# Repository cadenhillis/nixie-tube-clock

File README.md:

# nixie-tube-clock

custom high-voltage boost power supply and nessesary drivers to control IN-12A and IN13 nixies with an adafruit itsybitsy nRF32

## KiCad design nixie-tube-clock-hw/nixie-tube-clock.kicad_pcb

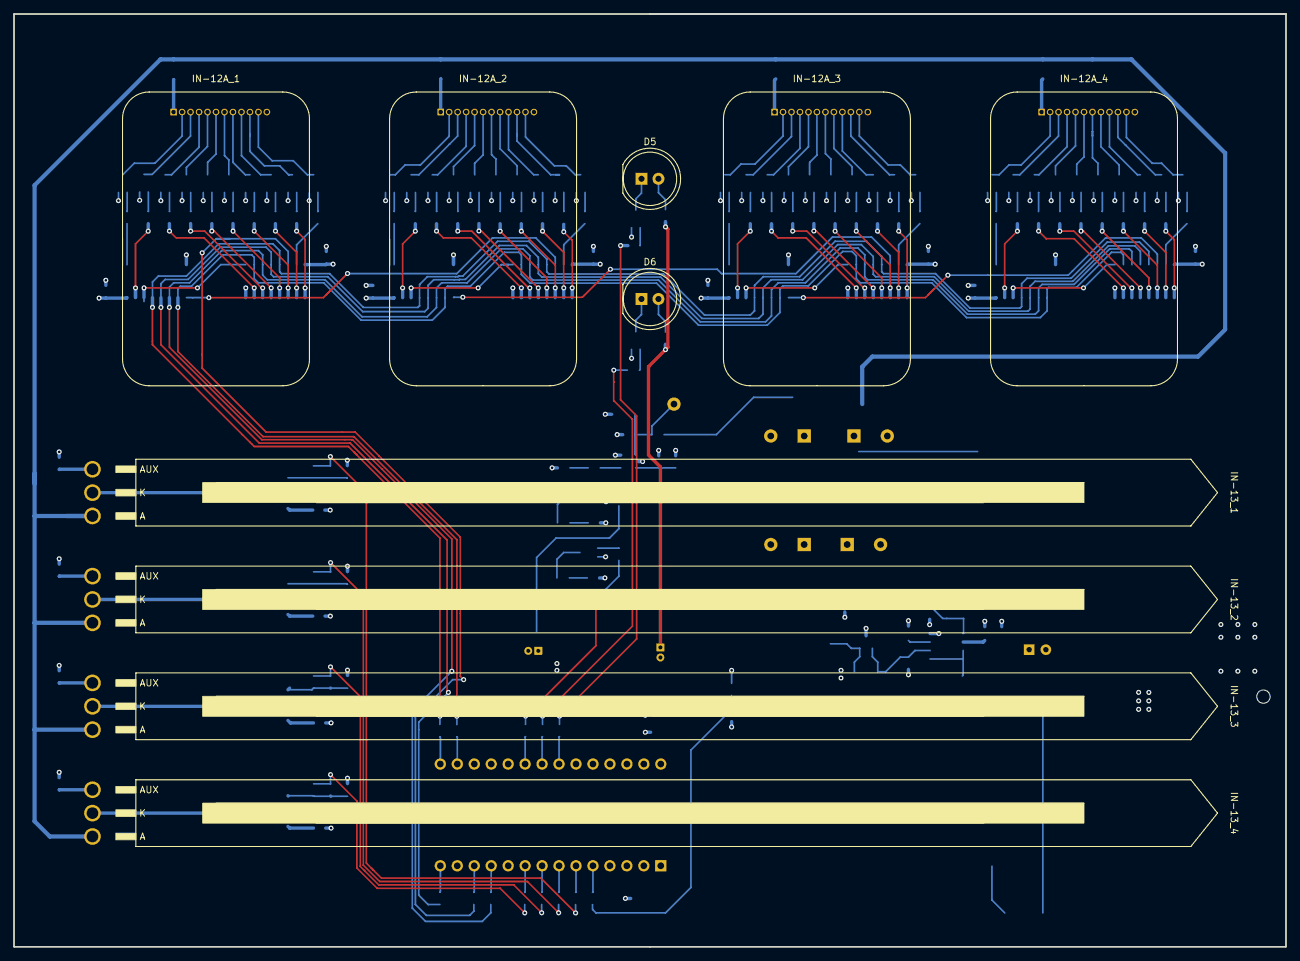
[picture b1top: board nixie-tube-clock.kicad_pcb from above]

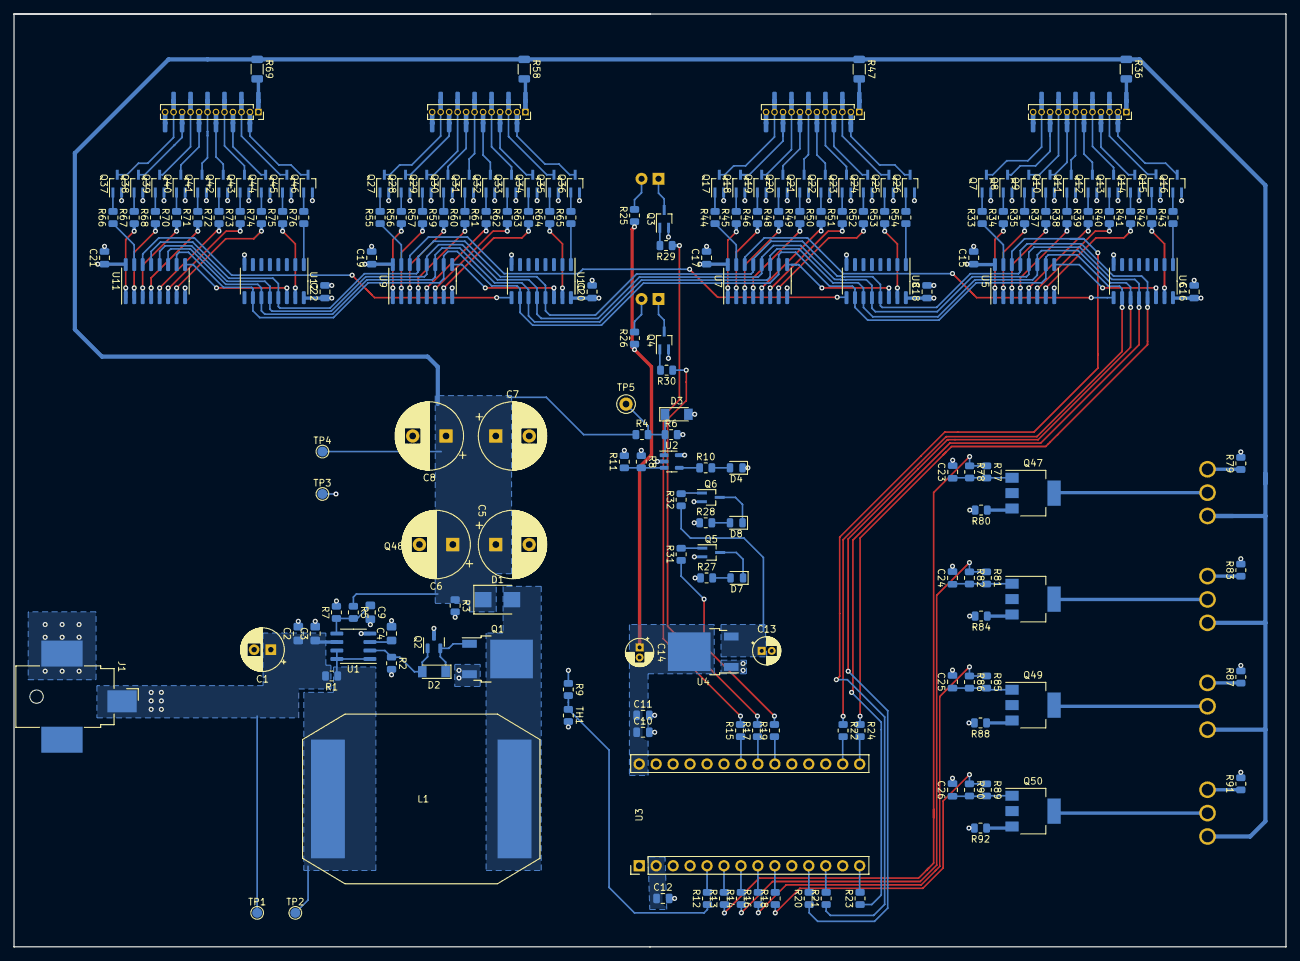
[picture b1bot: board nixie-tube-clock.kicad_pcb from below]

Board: 4 copper layers, 190.5 x 139.7 mm, 204 parts (194 on the bottom side), 200 nets.

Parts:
C1: 47uF; CP_Radial_D6.3mm_P2.50mm
C2: 2.2uF; C_0805_2012Metric_Pad1.18x1.45mm_HandSolder
C3: 0.1uF; C_0805_2012Metric_Pad1.18x1.45mm_HandSolder
C4: 470pF; C_0805_2012Metric_Pad1.18x1.45mm_HandSolder
C5, C6, C7, C8: 4.7uF; CP_Radial_D10.0mm_P5.00mm
C9: 10nF; C_0805_2012Metric_Pad1.18x1.45mm_HandSolder
C10: 1uF; C_0805_2012Metric
C11, C12, C23, C24, C25, C26: 10uF; C_0805_2012Metric
C13, C14: 10uF; CP_Radial_D4.0mm_P1.50mm
C15, C16, C17, C18, C19, C20, C21, C22: 0.1uF; C_0805_2012Metric
D1: SK3200B-LTP; D_SMB
D2: FDLL4148-D87Z; D_MiniMELF
D3: BZV55-C3V3,115; D_MiniMELF
D4, D8: ORANGE; D_0805_2012Metric
D5, D6: ORANGE; LED_D8.0mm
D7: RED; D_0805_2012Metric
IN-12A_1, IN-12A_2, IN-12A_3, IN-12A_4: IN-12A DAUGHTER; nixie_daughter
IN-13_1, IN-13_2, IN-13_3, IN-13_4: IN13; IN-13
J1: PJ-036AH-SMT-TR; BarrelJack_CUI_PJ-036AH-SMT_Horizontal
L1: 1mH; PM2120
Q1: FQD16N25CTM; TO-252-2
Q2: PMBT3906,235; SOT-23
Q3, Q4, Q5, Q6, Q7, Q8, Q9, Q10, Q11, Q12, Q13, Q14, Q15, Q16, Q17, Q18, Q19, Q20, Q21, Q22, Q23, Q24, Q25, Q26, Q27, Q28, Q29, Q30, Q31, Q32, Q33, Q34, Q35, Q36, Q37, Q38, Q39, Q40, Q41, Q42, Q43, Q44, Q45, Q46: MMSTA42-7-F; SOT-323_SC-70_Handsoldering
Q47, Q48, Q49, Q50: FZT857TA; SOT-223-3_TabPin2
R1: 300mR; R_0805_2012Metric
R2: 240; R_0805_2012Metric
R3: 1M; R_0805_2012Metric
R4: 3Meg; R_0805_2012Metric
R5: 200k; R_0805_2012Metric
R6: 20k; R_0805_2012Metric
R7: 1.68k; R_0805_2012Metric
R8: 25k; R_0805_2012Metric
R9, R11: 10k; R_0805_2012Metric
R10, R27, R28: 1.2k; R_0805_2012Metric
R12, R13, R14, R15, R16, R17, R18, R19, R20, R21, R22, R23, R24: 0; R_0805_2012Metric
R25, R26: 220; R_0805_2012Metric
R29, R30, R31: 1.2K; R_0805_2012Metric
R32: 10K; R_0805_2012Metric
R33, R34, R35, R37, R38, R39, R40, R41, R42, R43, R44, R45, R46, R48, R49, R50, R51, R52, R53, R54, R55, R56, R57, R59, R60, R61, R62, R63, R64, R65, R66, R67, R68, R70, R71, R72, R73, R74, R75, R76: 22k; R_0805_2012Metric
R36, R47, R58, R69: R_US; R_1206_3216Metric
R77, R81, R85, R89: 330; R_0805_2012Metric
R78, R82, R86, R90: 4.7k; R_0805_2012Metric
R79, R83, R87, R91: 330k; R_0805_2012Metric
R80, R84, R88, R92: 560; R_0805_2012Metric
TH1: 10k; R_0805_2012Metric
TP1, TP2, TP3, TP4: TestPoint; TestPoint_Pad_D1.5mm
TP5: TestPoint; TestPoint_Keystone_5000-5004_Miniature
U1: MC34063AD; SOIC-8_3.9x4.9mm_P1.27mm
U2: AS321KTR-G1; SOT-23-5
U3: ItsyBitsy_M0_Express; ItsyBitsy
U4: NCP1117IDT50T4G; TO-252-2
U5, U6, U7, U8, U9, U10, U11, U12: 74HC594D,118; SOIC-16_3.9x9.9mm_P1.27mm

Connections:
+3V3: C12.1, C15.1, C16.1, C17.1, C18.1, C19.1, C20.1, C21.1, C22.1, R8.1, R9.1, R27.1, R28.1, U2.5 (V+), U3.2 (3V3), U5.16 (VCC), U6.16 (VCC), U7.16 (VCC), U8.16 (VCC), U9.16 (VCC), U10.16 (VCC), U11.16 (VCC), U12.16 (VCC)
+5V: C10.1, C11.1, C14.1, R25.1, R26.1, U3.28 (BAT), U4.2 (VO)
+12V: C1.1, C2.1, C3.1, C13.1, J1.1, R1.2, R32.1, TP1.1, U1.6 (Vin), U4.3 (VI)
/150V_VA/1v_LED: D3.1 (K), R4.2, R6.1, TP5.1, U2.1 (+)
/COLON_1: R15.2, R29.1
/COLON_2: R17.2, R30.1
/D1/B0: R43.1, U6.1 (Q1)
/D1/B1: R33.1, U5.15 (Q0)
/D1/B2: R34.1, U5.1 (Q1)
/D1/B3: R35.1, U5.2 (Q2)
/D1/B4: R37.1, U5.3 (Q3)
/D1/B5: R38.1, U5.4 (Q4)
/D1/B6: R39.1, U5.5 (Q5)
/D1/B7: R40.1, U5.6 (Q6)
/D1/B8: R41.1, U5.7 (Q7)
/D1/B9: R42.1, U6.15 (Q0)
/D1/DOUT: U6.9 (Q7S), U7.14 (DS)
/D1/K0: IN-12A_1.2 (K_0), Q16.3 (C)
/D1/K1: IN-12A_1.11 (K_1), Q7.3 (C)
/D1/K2: IN-12A_1.10 (K_2), Q8.3 (C)
/D1/K3: IN-12A_1.9 (K_3), Q9.3 (C)
/D1/K4: IN-12A_1.8 (K_4), Q10.3 (C)
/D1/K5: IN-12A_1.7 (K_5), Q11.3 (C)
/D1/K6: IN-12A_1.6 (K_6), Q12.3 (C)
/D1/K7: IN-12A_1.5 (K_7), Q13.3 (C)
/D1/K8: IN-12A_1.4 (K_8), Q14.3 (C)
/D1/K9: IN-12A_1.3 (K_9), Q15.3 (C)
/D2/B0: R54.1, U8.1 (Q1)
/D2/B1: R44.1, U7.15 (Q0)
/D2/B2: R45.1, U7.1 (Q1)
/D2/B3: R46.1, U7.2 (Q2)
/D2/B4: R48.1, U7.3 (Q3)
/D2/B5: R49.1, U7.4 (Q4)
/D2/B6: R50.1, U7.5 (Q5)
/D2/B7: R51.1, U7.6 (Q6)
/D2/B8: R52.1, U7.7 (Q7)
/D2/B9: R53.1, U8.15 (Q0)
/D2/DOUT: U8.9 (Q7S), U9.14 (DS)
/D2/K0: IN-12A_2.2 (K_0), Q26.3 (C)
/D2/K1: IN-12A_2.11 (K_1), Q17.3 (C)
/D2/K2: IN-12A_2.10 (K_2), Q18.3 (C)
/D2/K3: IN-12A_2.9 (K_3), Q19.3 (C)
/D2/K4: IN-12A_2.8 (K_4), Q20.3 (C)
/D2/K5: IN-12A_2.7 (K_5), Q21.3 (C)
/D2/K6: IN-12A_2.6 (K_6), Q22.3 (C)
/D2/K7: IN-12A_2.5 (K_7), Q23.3 (C)
/D2/K8: IN-12A_2.4 (K_8), Q24.3 (C)
/D2/K9: IN-12A_2.3 (K_9), Q25.3 (C)
/D3/B0: R65.1, U10.1 (Q1)
/D3/B1: R55.1, U9.15 (Q0)
/D3/B2: R56.1, U9.1 (Q1)
/D3/B3: R57.1, U9.2 (Q2)
/D3/B4: R59.1, U9.3 (Q3)
/D3/B5: R60.1, U9.4 (Q4)
/D3/B6: R61.1, U9.5 (Q5)
/D3/B7: R62.1, U9.6 (Q6)
/D3/B8: R63.1, U9.7 (Q7)
/D3/B9: R64.1, U10.15 (Q0)
/D3/DOUT: U10.9 (Q7S), U11.14 (DS)
/D3/K0: IN-12A_3.2 (K_0), Q36.3 (C)
/D3/K1: IN-12A_3.11 (K_1), Q27.3 (C)
/D3/K2: IN-12A_3.10 (K_2), Q28.3 (C)
/D3/K3: IN-12A_3.9 (K_3), Q29.3 (C)
/D3/K4: IN-12A_3.8 (K_4), Q30.3 (C)
/D3/K5: IN-12A_3.7 (K_5), Q31.3 (C)
/D3/K6: IN-12A_3.6 (K_6), Q32.3 (C)
/D3/K7: IN-12A_3.5 (K_7), Q33.3 (C)
/D3/K8: IN-12A_3.4 (K_8), Q34.3 (C)
/D3/K9: IN-12A_3.3 (K_9), Q35.3 (C)
/D4/B0: R76.1, U12.1 (Q1)
/D4/B1: R66.1, U11.15 (Q0)
/D4/B2: R67.1, U11.1 (Q1)
/D4/B3: R68.1, U11.2 (Q2)
/D4/B4: R70.1, U11.3 (Q3)
/D4/B5: R71.1, U11.4 (Q4)
/D4/B6: R72.1, U11.5 (Q5)
/D4/B7: R73.1, U11.6 (Q6)
/D4/B8: R74.1, U11.7 (Q7)
/D4/B9: R75.1, U12.15 (Q0)
/D4/K0: IN-12A_4.2 (K_0), Q46.3 (C)
/D4/K1: IN-12A_4.11 (K_1), Q37.3 (C)
/D4/K2: IN-12A_4.10 (K_2), Q38.3 (C)
/D4/K3: IN-12A_4.9 (K_3), Q39.3 (C)
/D4/K4: IN-12A_4.8 (K_4), Q40.3 (C)
/D4/K5: IN-12A_4.7 (K_5), Q41.3 (C)
/D4/K6: IN-12A_4.6 (K_6), Q42.3 (C)
/D4/K7: IN-12A_4.5 (K_7), Q43.3 (C)
/D4/K8: IN-12A_4.4 (K_8), Q44.3 (C)
/D4/K9: IN-12A_4.3 (K_9), Q45.3 (C)
/DAY_PWM: R13.1, R77.1, R78.1
/MONTH_PWM: R16.1, R85.1, R86.1
/MOSI: R21.1, U5.14 (DS)
/SCK: R20.1, U5.11 (SHCP), U6.11 (SHCP), U7.11 (SHCP), U8.11 (SHCP), U9.11 (SHCP), U10.11 (SHCP), U11.11 (SHCP), U12.11 (SHCP)
/STORE: R23.1, U5.12 (STCP), U6.12 (STCP), U7.12 (STCP), U8.12 (STCP), U9.12 (STCP), U10.12 (STCP), U11.12 (STCP), U12.12 (STCP)
/TEMP: R9.2, R12.1, TH1.1
/TEMP_LED: R19.2, R31.1
/WEEK_PWM: R14.1, R81.1, R82.1
/YEAR_PWM: R18.1, R89.1, R90.1
/~CLR_SHIFT: R22.1, U5.10 (~SHR), U6.10 (~SHR), U7.10 (~SHR), U8.10 (~SHR), U9.10 (~SHR), U10.10 (~SHR), U11.10 (~SHR), U12.10 (~SHR)
/~CLR_STORE: R24.1, U5.13 (~STR), U6.13 (~STR), U7.13 (~STR), U8.13 (~STR), U9.13 (~STR), U10.13 (~STR), U11.13 (~STR), U12.13 (~STR)
GND: C1.2, C2.2, C3.2, C4.2, C5.2, C6.2, C7.2, C8.2, C9.2, C10.2, C11.2, C12.2, C13.2, C14.2, C15.2, C16.2, C17.2, C18.2, C19.2, C20.2, C21.2, C22.2, C23.2, C24.2, C25.2, C26.2, D3.2 (A), D4.1 (K), J1.2, Q1.3 (S), Q2.3 (C), Q3.2 (E), Q4.2 (E), Q5.2 (E), Q6.2 (E), Q7.2 (E), Q8.2 (E), Q9.2 (E), Q10.2 (E), Q11.2 (E), Q12.2 (E), Q13.2 (E), Q14.2 (E), Q15.2 (E), Q16.2 (E), Q17.2 (E), Q18.2 (E), Q19.2 (E), Q20.2 (E), Q21.2 (E), Q22.2 (E), Q23.2 (E), Q24.2 (E), Q25.2 (E), Q26.2 (E), Q27.2 (E), Q28.2 (E), Q29.2 (E), Q30.2 (E), Q31.2 (E), Q32.2 (E), Q33.2 (E), Q34.2 (E), Q35.2 (E), Q36.2 (E), Q37.2 (E), Q38.2 (E), Q39.2 (E), Q40.2 (E), Q41.2 (E), Q42.2 (E), Q43.2 (E), Q44.2 (E), Q45.2 (E), Q46.2 (E), R2.2, R3.2, R6.2, R7.2, R11.2, R79.2, R80.2, R83.2, R84.2, R87.2, R88.2, R91.2, R92.2, TH1.2, TP3.1, U1.4 (GND), U2.2 (V-), U3.27 (G), U4.1 (ADJ), U5.8 (GND), U6.8 (GND), U7.8 (GND), U8.8 (GND), U9.8 (GND), U10.8 (GND), U11.8 (GND), U12.8 (GND)
unnamed: C4.1, U1.3 (TC)
unnamed: C9.1, R5.2, R7.1, U1.5 (Vfb)
unnamed: C23.1, Q47.1 (B), R77.2, R78.2
unnamed: C24.1, Q48.1 (B), R81.2, R82.2
unnamed: C25.1, Q49.1 (B), R85.2, R86.2
unnamed: C26.1, Q50.1 (B), R89.2, R90.2
unnamed: D1.2 (A), L1.2, Q1.2 (D)
unnamed: D2.1 (K), Q1.1 (G), Q2.2 (E)
unnamed: D2.2 (A), Q2.1 (B), R2.1, U1.2 (SwE)
unnamed: D4.2 (A), R10.2
unnamed: D5.1 (K), Q3.3 (C)
unnamed: D5.2 (A), R25.2
unnamed: D6.1 (K), Q4.3 (C)
unnamed: D6.2 (A), R26.2
unnamed: D7.1 (K), Q5.3 (C)
unnamed: D7.2 (A), R27.2
unnamed: D8.1 (K), Q6.3 (C)
unnamed: D8.2 (A), R28.2
unnamed: IN-12A_1.1 (A), R36.2
unnamed: IN-12A_2.1 (A), R47.2
unnamed: IN-12A_3.1 (A), R58.2
unnamed: IN-12A_4.1 (A), R69.2
unnamed: IN-13_1.1, R79.1
unnamed: IN-13_1.2, Q47.2 (C)
unnamed: IN-13_2.1, R83.1
unnamed: IN-13_2.2, Q48.2 (C)
unnamed: IN-13_3.1, R87.1
unnamed: IN-13_3.2, Q49.2 (C)
unnamed: IN-13_4.1, R91.1
unnamed: IN-13_4.2, Q50.2 (C)
unnamed: L1.1, R1.1, TP2.1, U1.1 (SwC), U1.7 (Ipk), U1.8 (DC)
unnamed: Q3.1 (B), R29.2
unnamed: Q4.1 (B), R30.2
unnamed: Q5.1 (B), R31.2
unnamed: Q6.1 (B), R32.2
unnamed: Q7.1 (B), R33.2
unnamed: Q8.1 (B), R34.2
unnamed: Q9.1 (B), R35.2
unnamed: Q10.1 (B), R37.2
unnamed: Q11.1 (B), R38.2
unnamed: Q12.1 (B), R39.2
unnamed: Q13.1 (B), R40.2
unnamed: Q14.1 (B), R41.2
unnamed: Q15.1 (B), R42.2
unnamed: Q16.1 (B), R43.2
unnamed: Q17.1 (B), R44.2
unnamed: Q18.1 (B), R45.2
unnamed: Q19.1 (B), R46.2
unnamed: Q20.1 (B), R48.2
unnamed: Q21.1 (B), R49.2
unnamed: Q22.1 (B), R50.2
unnamed: Q23.1 (B), R51.2
unnamed: Q24.1 (B), R52.2
unnamed: Q25.1 (B), R53.2
unnamed: Q26.1 (B), R54.2
unnamed: Q27.1 (B), R55.2
unnamed: Q28.1 (B), R56.2
unnamed: Q29.1 (B), R57.2
unnamed: Q30.1 (B), R59.2
unnamed: Q31.1 (B), R60.2
unnamed: Q32.1 (B), R61.2
unnamed: Q33.1 (B), R62.2
unnamed: Q34.1 (B), R63.2
unnamed: Q35.1 (B), R64.2
unnamed: Q36.1 (B), R65.2
unnamed: Q37.1 (B), R66.2
unnamed: Q38.1 (B), R67.2
unnamed: Q39.1 (B), R68.2
unnamed: Q40.1 (B), R70.2
unnamed: Q41.1 (B), R71.2
unnamed: Q42.1 (B), R72.2
unnamed: Q43.1 (B), R73.2
unnamed: Q44.1 (B), R74.2
unnamed: Q45.1 (B), R75.2
unnamed: Q46.1 (B), R76.2
unnamed: Q47.3 (E), R80.1
unnamed: Q48.3 (E), R84.1
unnamed: Q49.3 (E), R88.1
unnamed: Q50.3 (E), R92.1
unnamed: R10.1, U2.4
unnamed: R8.2, R11.1, U2.3 (-)
unnamed: R12.2, U3.5 (A0)
unnamed: R13.2, U3.6 (A1)
unnamed: R14.2, U3.7 (A2)
unnamed: R15.1, U3.22 (10)
unnamed: R16.2, U3.8 (A3)
unnamed: R17.1, U3.21 (9)
unnamed: R18.2, U3.9 (A4)
unnamed: R19.1, U3.20 (7)
unnamed: R20.2, U3.11 (SCK)
unnamed: R21.2, U3.12 (MO)
unnamed: R22.2, U3.16 (1_TX)
unnamed: R23.2, U3.14 (D2)
unnamed: R24.2, U3.15 (0_RX)
unnamed: U5.9 (Q7S), U6.14 (DS)
unnamed: U7.9 (Q7S), U8.14 (DS)
unnamed: U9.9 (Q7S), U10.14 (DS)
unnamed: U11.9 (Q7S), U12.14 (DS)
VAA: C5.1, C6.1, C7.1, C8.1, D1.1 (K), IN-13_1.3, IN-13_2.3, IN-13_3.3, IN-13_4.3, R3.1, R4.1, R5.1, R36.1, R47.1, R58.1, R69.1, TP4.1

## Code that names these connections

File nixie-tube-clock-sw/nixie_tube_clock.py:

import board
import analogio, digitalio, pwmio, busio
from adafruit_ble import BLERadio
from adafruit_ble.advertising.standard import SolicitServicesAdvertisement
from adafruit_ble.services.standard import CurrentTimeService
from adafruit_ble.services.nordic import UARTService
import rtc
import time as t

class nixie_tube_clock:

    digit_dict = {   # bit of shift register
        0 : b'\x02\x00', # bit 9
        1 : b'\x00\x01', # bit 0 
        2 : b'\x00\x02', # bit 1
        3 : b'\x00\x04', # bit 2
        4 : b'\x00\x08', # bit 3
        5 : b'\x00\x10', # bit 4
        6 : b'\x00\x20', # bit 5
        7 : b'\x00\x40', # bit 6
        8 : b'\x00\x80', # bit 7
        9 : b'\x01\x00', # bit 8
        }  

    def __init__(self):

        #dio
        self.store = digitalio.DigitalInOut(board.D2)
        self.store.direction = digitalio.Direction.OUTPUT
        self.store.value = False

        self.clr_shift_n = digitalio.DigitalInOut(board.TX)
        self.clr_shift_n.direction = digitalio.Direction.OUTPUT
        self.clr_shift_n.value = True

        self.clr_store_n = digitalio.DigitalInOut(board.RX)
        self.clr_store_n.direction = digitalio.Direction.OUTPUT
        self.clr_store_n.value = True

        self.colon1 = pwmio.PWMOut(board.D10)
        self.colon1.duty_cycle = int(65535*0.01)

        self.colon2 = pwmio.PWMOut(board.D9)
        self.colon2.duty_cycle = int(65535*0.01)

        self.temp_led = digitalio.DigitalInOut(board.D7)
        self.temp_led.direction = digitalio.Direction.OUTPUT
        self.temp_led.value = False

        #pwm
        self.day_pwm = pwmio.PWMOut(board.A1)
        self.day_pwm.duty_cycle = 0
        self.week_pwm = pwmio.PWMOut(board.A2)
        self.week_pwm.duty_cycle = 0
        self.month_pwm = pwmio.PWMOut(board.A3)
        self.month_pwm.duty_cycle = 0
        self.year_pwm = pwmio.PWMOut(board.A4)
        self.year_pwm.duty_cycle = 0

        #ain
        #self.temp_ntc = analogio.AnalogIn(board.A0)
        #temp = temp_ntc.value * x x x x x
        
        #values
        # time init
        self.r = rtc.RTC()
        #look for file
        self.r.datetime = t.struct_time((2022, 4, 25, 13, 30, 0, 0, -1, -1))

        #ble
        self.ble = BLERadio()
        self.uart = UARTService()
        self.advertisement = SolicitServicesAdvertisement()
        self.advertisement.complete_name = "TimePlease:-)"
        self.advertisement.solicited_services.append(CurrentTimeService)
        self.ble.start_advertising(self.advertisement)
   
    def update_display(self):
        #assemble bytearray
        if self.r.datetime[3] > 12:
            temp = self.r.datetime[3]-12
        else:
            temp = self.r.datetime[3]
        mod_h = temp % 10
        mod_m = self.r.datetime[4] % 10
        self.SEND_BUF = self.digit_dict[mod_m] + self.digit_dict[(self.r.datetime[4] - mod_m) / 10] + self.digit_dict[mod_h] + self.digit_dict[(temp - mod_h) / 10] 
        #print(self.SEND_BUF)
        self.write_74hc594d()
        self.write_pwm()
    
    def write_74hc594d(self):
        #re-init spi
        spi = busio.SPI(clock=board.SCK, MOSI=board.MOSI)
        while not spi.try_lock():
            pass
        spi.configure(baudrate = 9600)
        #send data
        #print(self.SEND_BUF)
        spi.write(self.SEND_BUF)
        spi.deinit()
        #pulse storage clk to store shift values
        self.store.value = False
        self.store.value = True
        self.store.value = False
        
    def write_pwm(self):
        #get yday
        leapday = self.r.datetime[7]
        year = self.r.datetime[0]
        #detect leap year
        if self.r.datetime[7] == 59:
            if float.is_integer((self.r.datetime[0] - 2020) / 4):
                self.r.datetime[7] = 60
                if self.r.datetime[6] == 0: self.r.datetime[6] = 6
                else: self.r.datetime[6] -= 1
        # write values
        self.day_pwm.duty_cycle = int(((self.r.datetime[3] * 60 + self.r.datetime[4])/1440) * 65535)
        self.week_pwm.duty_cycle = int(((self.r.datetime[3] * 60 + self.r.datetime[4] + (self.r.datetime[6]+ 1) * 24 * 60) / 10080) * 65535)
        self.month_pwm.duty_cycle = int(self.r.datetime[2]/31 * 65535) #assuming 31 days a month bec im lazy
        self.year_pwm.duty_cycle = int(self.r.datetime[7]/366 * 65535)

    def ble_time(self):
        while not self.ble.connected:
            self.update_display()
            t.sleep(10)
            pass
        self.ble.stop_advertising()
        print("connected")

        while self.ble.connected:
            for connection in self.ble.connections:
                if not connection.paired:
                    connection.pair()
                    print("paired")
                cts = connection[CurrentTimeService]
                self.r.datetime = cts.struct_time
                print(self.r.datetime)
                self.update_display()
                t.sleep(10)
                

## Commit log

2022-02-12 layout and routing
2022-02-14 fab stuff
2022-03-13 minor board / part changes
2022-04-25 el fin
2022-04-27 bug fix
